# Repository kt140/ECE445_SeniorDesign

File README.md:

# ECE 445: Senior Design - Team 7

## 	Project - Optimized solar charging off grid for several output voltage potentials

This is the senior design project for Kanin Tangchartsiri (kanint2), Lukas Gollings (lwg2), and Wonjoon Lee (wonjoon2).

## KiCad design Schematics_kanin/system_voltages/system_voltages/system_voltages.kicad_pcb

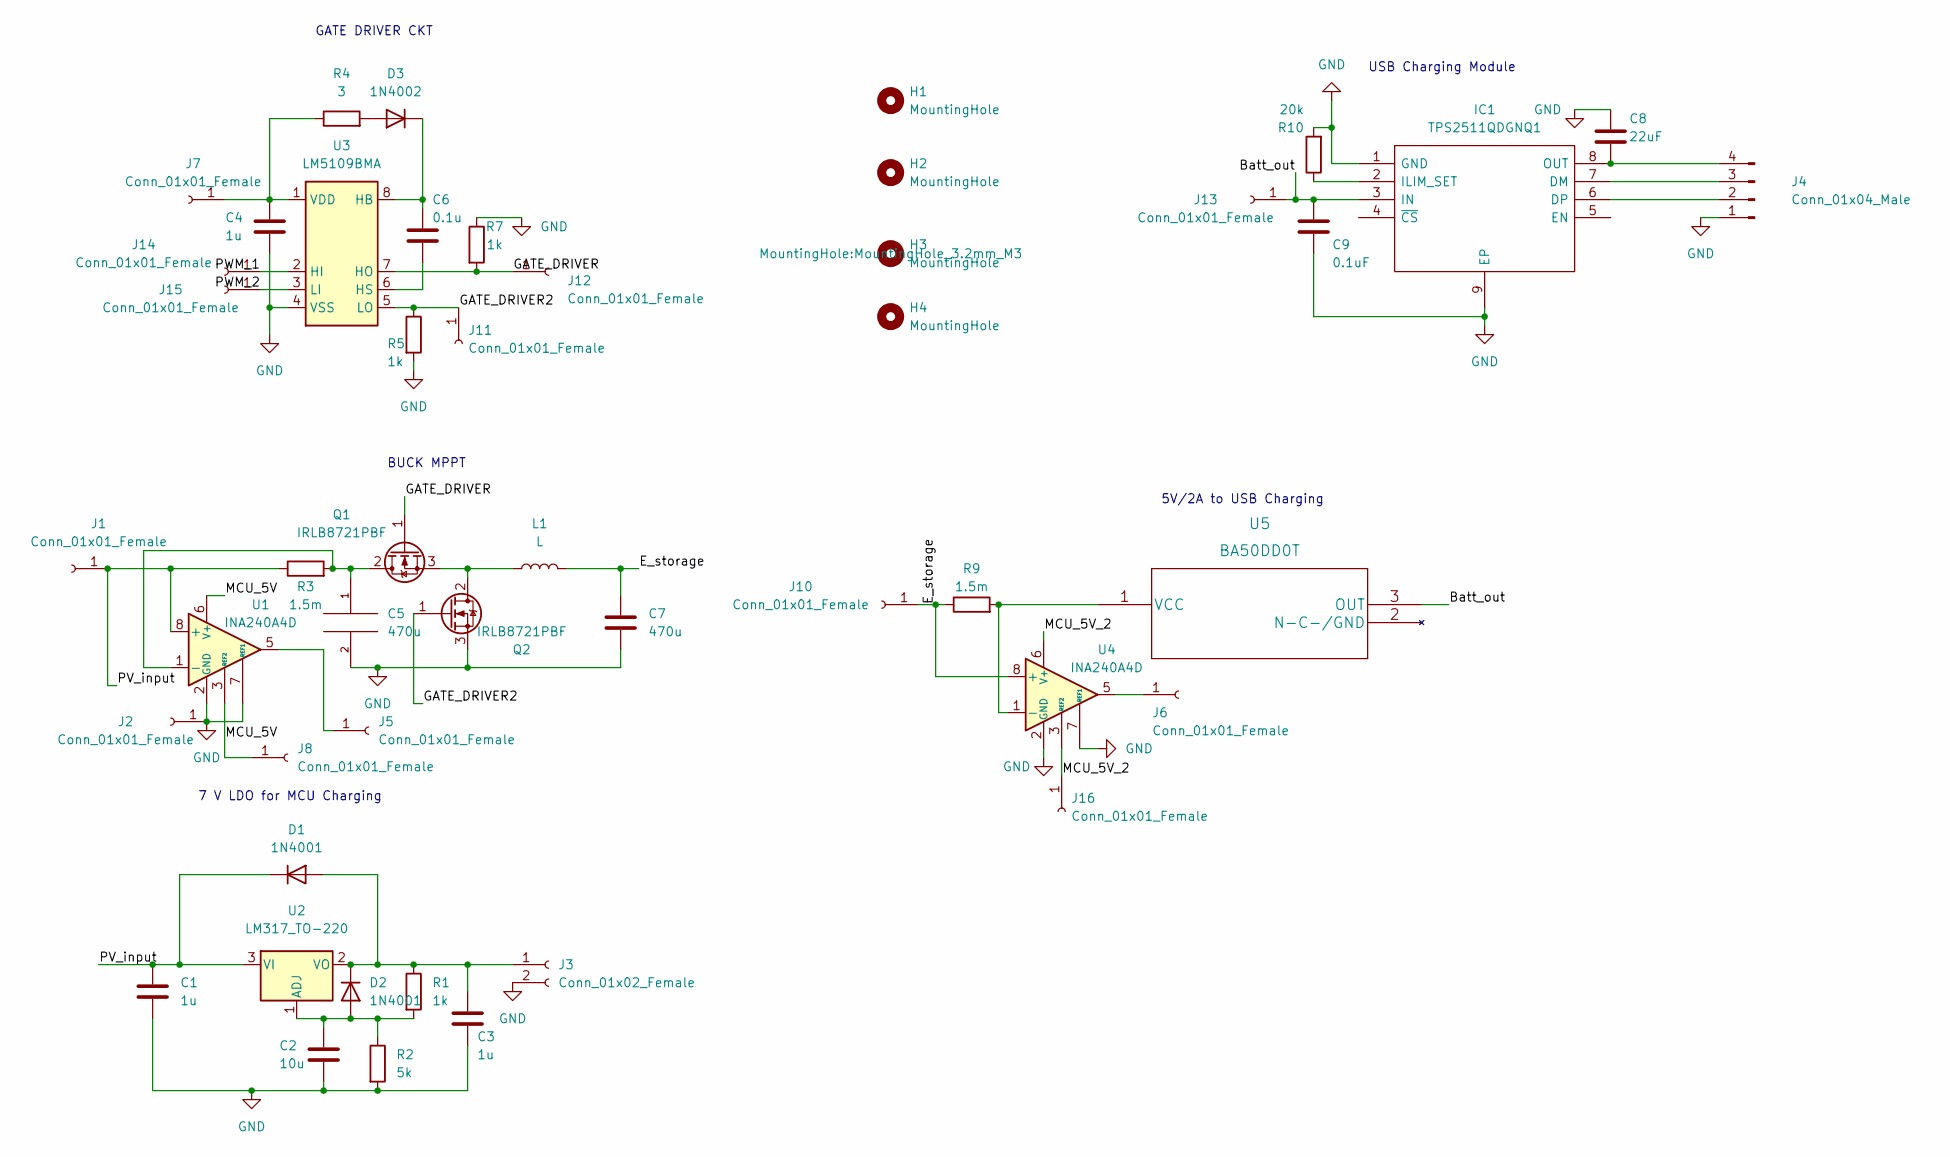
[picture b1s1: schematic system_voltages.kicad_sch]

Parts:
C1, C3, C4: 1u; C_0805_2012Metric_Pad1.18x1.45mm_HandSolder
C2: 10u; C_1210_3225Metric_Pad1.33x2.70mm_HandSolder
C5, C7: 470u; CP_Radial_D10.0mm_P5.00mm
C6: 0.1u; C_1206_3216Metric_Pad1.33x1.80mm_HandSolder
C8: 22uF; CP_Radial_D8.0mm_P5.00mm
C9: 0.1uF; C_1206_3216Metric_Pad1.33x1.80mm_HandSolder
D1, D2: 1N4001; D_DO-41_SOD81_P10.16mm_Horizontal
D3: 1N4002; D_DO-41_SOD81_P10.16mm_Horizontal
H1, H2, H3, H4: MountingHole; MountingHole_3.2mm_M3
IC1: TPS2511QDGNQ1; SOP65P490X110-9N; Mouser Part Number 595-TPS2511QDGNQ1
J1, J2: Conn_01x01_Female; Banana_Jack_1Pin
J3: Conn_01x02_Female; PhoenixContact_MSTBVA_2,5_3-G_1x03_P5.00mm_Vertical
J4: Conn_01x04_Male; PinHeader_1x04_P2.54mm_Vertical
J5, J6, J7, J8, J10, J11, J12, J13, J14, J15, J16: Conn_01x01_Female; Pin_D1.0mm_L10.0mm
L1: L; L_Toroid_Vertical_L35.1mm_W21.1mm_P18.50mm_Vishay_TJ6
Q1, Q2: IRLB8721PBF; TO-220-3_Vertical
R1: 1k; R_Axial_DIN0516_L15.5mm_D5.0mm_P25.40mm_Horizontal
R2: 5k; R_Axial_DIN0617_L17.0mm_D6.0mm_P20.32mm_Horizontal
R3, R9: 1.5m; R_2512_6332Metric_Pad1.40x3.35mm_HandSolder
R4: 3; R_2010_5025Metric_Pad1.40x2.65mm_HandSolder
R5, R7: 1k; R_0805_2012Metric_Pad1.20x1.40mm_HandSolder
R10: 20k; R_Axial_DIN0207_L6.3mm_D2.5mm_P10.16mm_Horizontal
U1, U4: INA240A4D; SOIC-8_3.9x4.9mm_P1.27mm
U2: LM317_TO-220; TO-220-3_Vertical
U3: LM5109BMA; SOIC-8_3.9x4.9mm_P1.27mm
U5: BA50DD0T

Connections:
/Batt_out: C9.1, IC1.3 (IN), J13.1, U5.3 (OUT)
/E_storage: C7.1, J10.1, L1.2, R9.1, U4.8 (+)
/GATE_DRIVER: J12.1, Q1.1 (G), R7.2, U3.7 (HO)
/GATE_DRIVER2: J11.1, Q2.1 (G), R5.1, U3.5 (LO)
/MCU_5V: J8.1, U1.3 (REF2), U1.6 (V+)
/MCU_5V_2: J16.1, U4.3 (REF2), U4.6 (V+)
/PV_input: C1.1, D1.1 (K), J1.1, R3.1, U1.8 (+), U2.3 (VI)
/PWM_1: J14.1, U3.2 (HI)
/PWM_2: J15.1, U3.3 (LI)
GND: C1.2, C2.2, C3.2, C4.2, C5.2, C7.2, C8.1, C9.2, IC1.1 (GND), IC1.9 (EP), J2.1, J3.2, J4.1, Q2.3 (S), R2.2, R5.2, R7.1, R10.2, U1.2 (GND), U1.4 (GND), U1.7 (REF1), U3.4 (VSS), U4.2 (GND), U4.4 (GND), U4.7 (REF1)
unnamed: C2.1, D2.2 (A), R1.2, R2.1, U2.1 (ADJ)
unnamed: C3.1, D1.2 (A), D2.1 (K), J3.1, R1.1, U2.2 (VO)
unnamed: C4.1, J7.1, R4.1, U3.1 (VDD)
unnamed: C5.1, Q1.2 (D), R3.2, U1.1 (-)
unnamed: C6.1, D3.1 (K), U3.8 (HB)
unnamed: C6.2, U3.6 (HS)
unnamed: C8.2, IC1.8 (OUT), J4.4
unnamed: IC1.2 (ILIM_SET), R10.1
unnamed: IC1.6 (DP), J4.2
unnamed: IC1.7 (DM), J4.3
unnamed: J5.1, U1.5
unnamed: J6.1, U4.5
unnamed: L1.1, Q1.3 (S), Q2.2 (D)
unnamed: D3.2 (A), R4.2
unnamed: R9.2, U4.1 (-), U5.1 (VCC)

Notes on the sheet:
BUCK MPPT
5V/2A to USB Charging
GATE DRIVER CKT
7 V LDO for MCU Charging
USB Charging Module

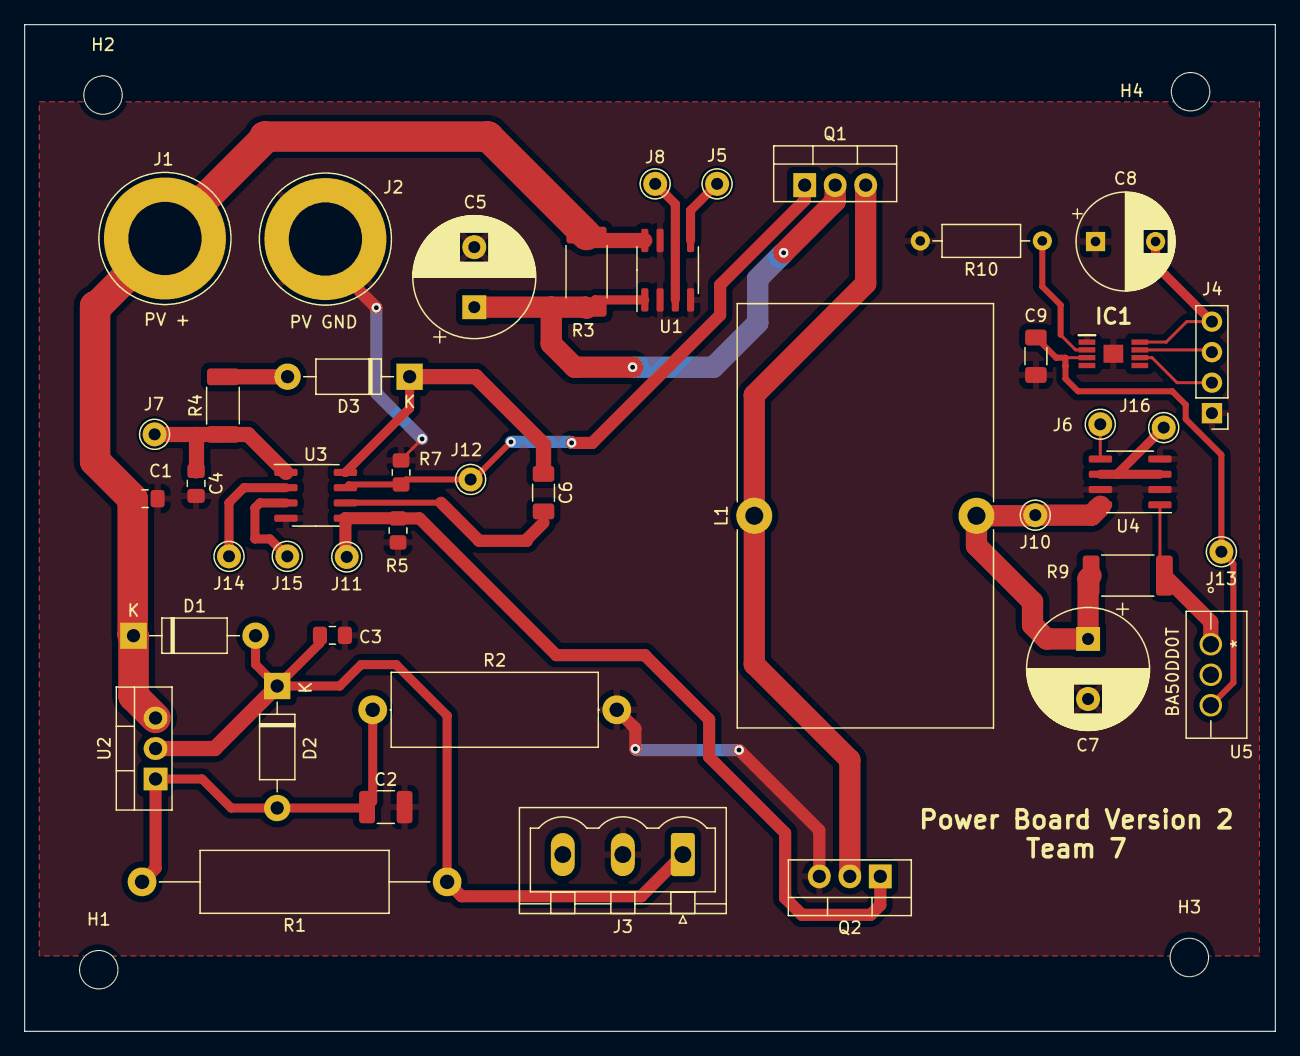
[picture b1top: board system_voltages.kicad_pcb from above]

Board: 2 copper layers, 104.1 x 83.8 mm, 48 parts (0 on the bottom side), 25 nets.

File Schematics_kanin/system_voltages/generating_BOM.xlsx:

Id | Designator | Package | Quantity | Designation | Supplier and ref | Column1 | _1
1 | R10 | R_Axial_DIN0207_L6.3mm_D2.5mm_P10.16mm_Horizontal | 1 | 20k
2 | C9 | C_1206_3216Metric_Pad1.33x1.80mm_HandSolder | 1 | 0.1uF
3 | R9,R3 | R_2512_6332Metric_Pad1.40x3.35mm_HandSolder | 2 | 1.5m
4 | C4,C3,C1 | C_0805_2012Metric_Pad1.18x1.45mm_HandSolder | 3 | 1u
5 | U5 | BA50DD0T | 1 | BA50DD0T
6 | D2,D1 | D_DO-41_SOD81_P10.16mm_Horizontal | 2 | 1N4001
7 | J1,J2 | Banana_Jack_1Pin | 2 | Conn_01x01_Female
8 | L1 | L_Toroid_Vertical_L35.1mm_W21.1mm_P18.50mm_Vishay_TJ6 | 1 | L
9 | J3 | PhoenixContact_MSTBVA_2,5_3-G_1x03_P5.00mm_Vertical | 1 | Conn_01x02_Female
10 | J6,J12,J14,J10,J8,J5,J16,J15,J13,J11,J7 | Pin_D1.0mm_L10.0mm | 11 | Conn_01x01_Female
11 | R2 | R_Axial_DIN0617_L17.0mm_D6.0mm_P20.32mm_Horizontal | 1 | 5k
12 | C2 | C_1210_3225Metric_Pad1.33x2.70mm_HandSolder | 1 | 10u
13 | U4,U1 | SOIC-8_3.9x4.9mm_P1.27mm | 2 | INA240A4D
14 | H4,H2,H3,H1 | MountingHole_3.2mm_M3 | 4 | MountingHole
15 | C6 | C_1206_3216Metric_Pad1.33x1.80mm_HandSolder | 1 | 0.1u
16 | R4 | R_2010_5025Metric_Pad1.40x2.65mm_HandSolder | 1 | 3
17 | C8 | CP_Radial_D8.0mm_P5.00mm | 1 | 22uF
18 | C5,C7 | CP_Radial_D10.0mm_P5.00mm | 2 | 470u
19 | J4 | PinHeader_1x04_P2.54mm_Vertical | 1 | Conn_01x04_Male
20 | R1 | R_Axial_DIN0516_L15.5mm_D5.0mm_P25.40mm_Horizontal | 1 | 1k
21 | U3 | SOIC-8_3.9x4.9mm_P1.27mm | 1 | LM5109BMA
22 | R5,R7 | R_0805_2012Metric_Pad1.20x1.40mm_HandSolder | 2 | 1k
23 | U2 | TO-220-3_Vertical | 1 | LM317_TO-220
24 | Q2,Q1 | TO-220-3_Vertical | 2 | IRLB8721PBF
25 | IC1 | SOP65P490X110-9N | 1 | TPS2511QDGNQ1
26 | D3 | D_DO-41_SOD81_P10.16mm_Horizontal | 1 | 1N4002

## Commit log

2022-02-15 Wanted to create Yei's folder
2022-02-15 Create place_holder
2022-02-17 wonjoon_notebook progress 1
2022-02-18 wonjoon_notebook progress 2 and Example Upload
2022-02-18 MCU Progress 1
2022-02-24 Pushing the files for simulation with PV simulation
2022-02-24 Added resources
2022-02-24 Added some extra MPPT resources
2022-02-25 Adding all of my simulations
2022-02-25 Adding Yei's log 2/25/22
2022-02-25 Added reference article regarding MPPT
2022-02-25 Woops
2022-02-25 Updated the front page readme
2022-02-25 Renamed Wonjoon's notebook to readme
2022-02-25 Added design doc check
2022-03-02 Adding a basic schematics folder
2022-03-10 Testing still from Bash terminal
2022-03-10 Still dont have access
2022-03-10 Added some kicad
2022-03-10 I think Git works
2022-03-12 Added 7 V circuit schematic
2022-03-12 Nearly done with 7V MCU ckt, need to size output cap
2022-03-13 Added new entry to worklog for Yei, Initial PCB Design
2022-03-17 Added a few values to schematic
2022-03-18 Adding new datasheet with LM5009 use cases
2022-03-20 Added new design for 7 V output
2022-03-20 Logged spring break work
2022-03-20 USB 5V/2A Research
2022-03-20 Images??
2022-03-21 WonJoon Notebook Updated, Simulation, Code updated
2022-03-21 Made some changes for system voltages
2022-03-22 Added entry to Kanin's log + finished schematic of MCU 7V
2022-03-23 Images work locally, not in repo
2022-03-23 Checking if image shows up
2022-03-23 More notebook entries copied to GitHub
2022-03-23 Notebook entries through March
2022-03-24 Updated 7 V MCU
2022-03-25 Added buck and USB charging
2022-03-26 Added 5V/2A LDO
2022-03-26 more pdf resources I have been using
2022-03-26 Pushing everything for Lukas
2022-03-27 Heat sink, some current sense, more references
2022-03-27 picture had wrong path
2022-03-27 Adding changes to kicad
2022-03-27 Added entry + gate drivers
2022-03-27 Adding changes to gate driver ckt
2022-03-28 Started routing our footprints
2022-04-06 Pushing again for updates
2022-04-06 Adding schematics for power board
2022-04-06 Added PCB work
2022-04-06 committed BOM and PCB changes
2022-04-12 Some images from IPR, more catching up
2022-04-12 more notebooks
2022-04-13 Almost updated my notebook with everything
2022-04-13 Old simulation
2022-04-14 Adding changes from photos of lab
2022-04-19 Added changes for 4/18/2022
2022-04-19 forgot to push
2022-04-25 Adding buck converter simulation images
2022-04-25 Adding photos for Yei's notebook
2022-04-26 code
2022-04-26 Adding changes to Yei's notebook
2022-04-27 Added entry for 04/19/2022 Yei
2022-04-27 Adding extra image
2022-04-27 added additional entries
2022-04-30 Adding entries on a late friday night
2022-04-30 Added most recent entry for whole design
2022-04-30 checking centering on gif
2022-04-30 centering gif
2022-05-01 wonjoon notebook update
2022-05-04 Making changes to readme
2022-05-04 Adding gate drivers
2022-05-04 Making changes for the night - Yei
2022-05-05 Have one last entry left + table of contents
2022-05-05 Done with notebook content, need to do table of contents. If not oh well
2022-05-05 Added table of contents
2022-05-05 final table of contents
2022-05-06 last notebook entry, still gotta format the Table of Contents
2022-05-06 More pictures
2022-05-06 Final Notebook
2022-05-06 Typos
